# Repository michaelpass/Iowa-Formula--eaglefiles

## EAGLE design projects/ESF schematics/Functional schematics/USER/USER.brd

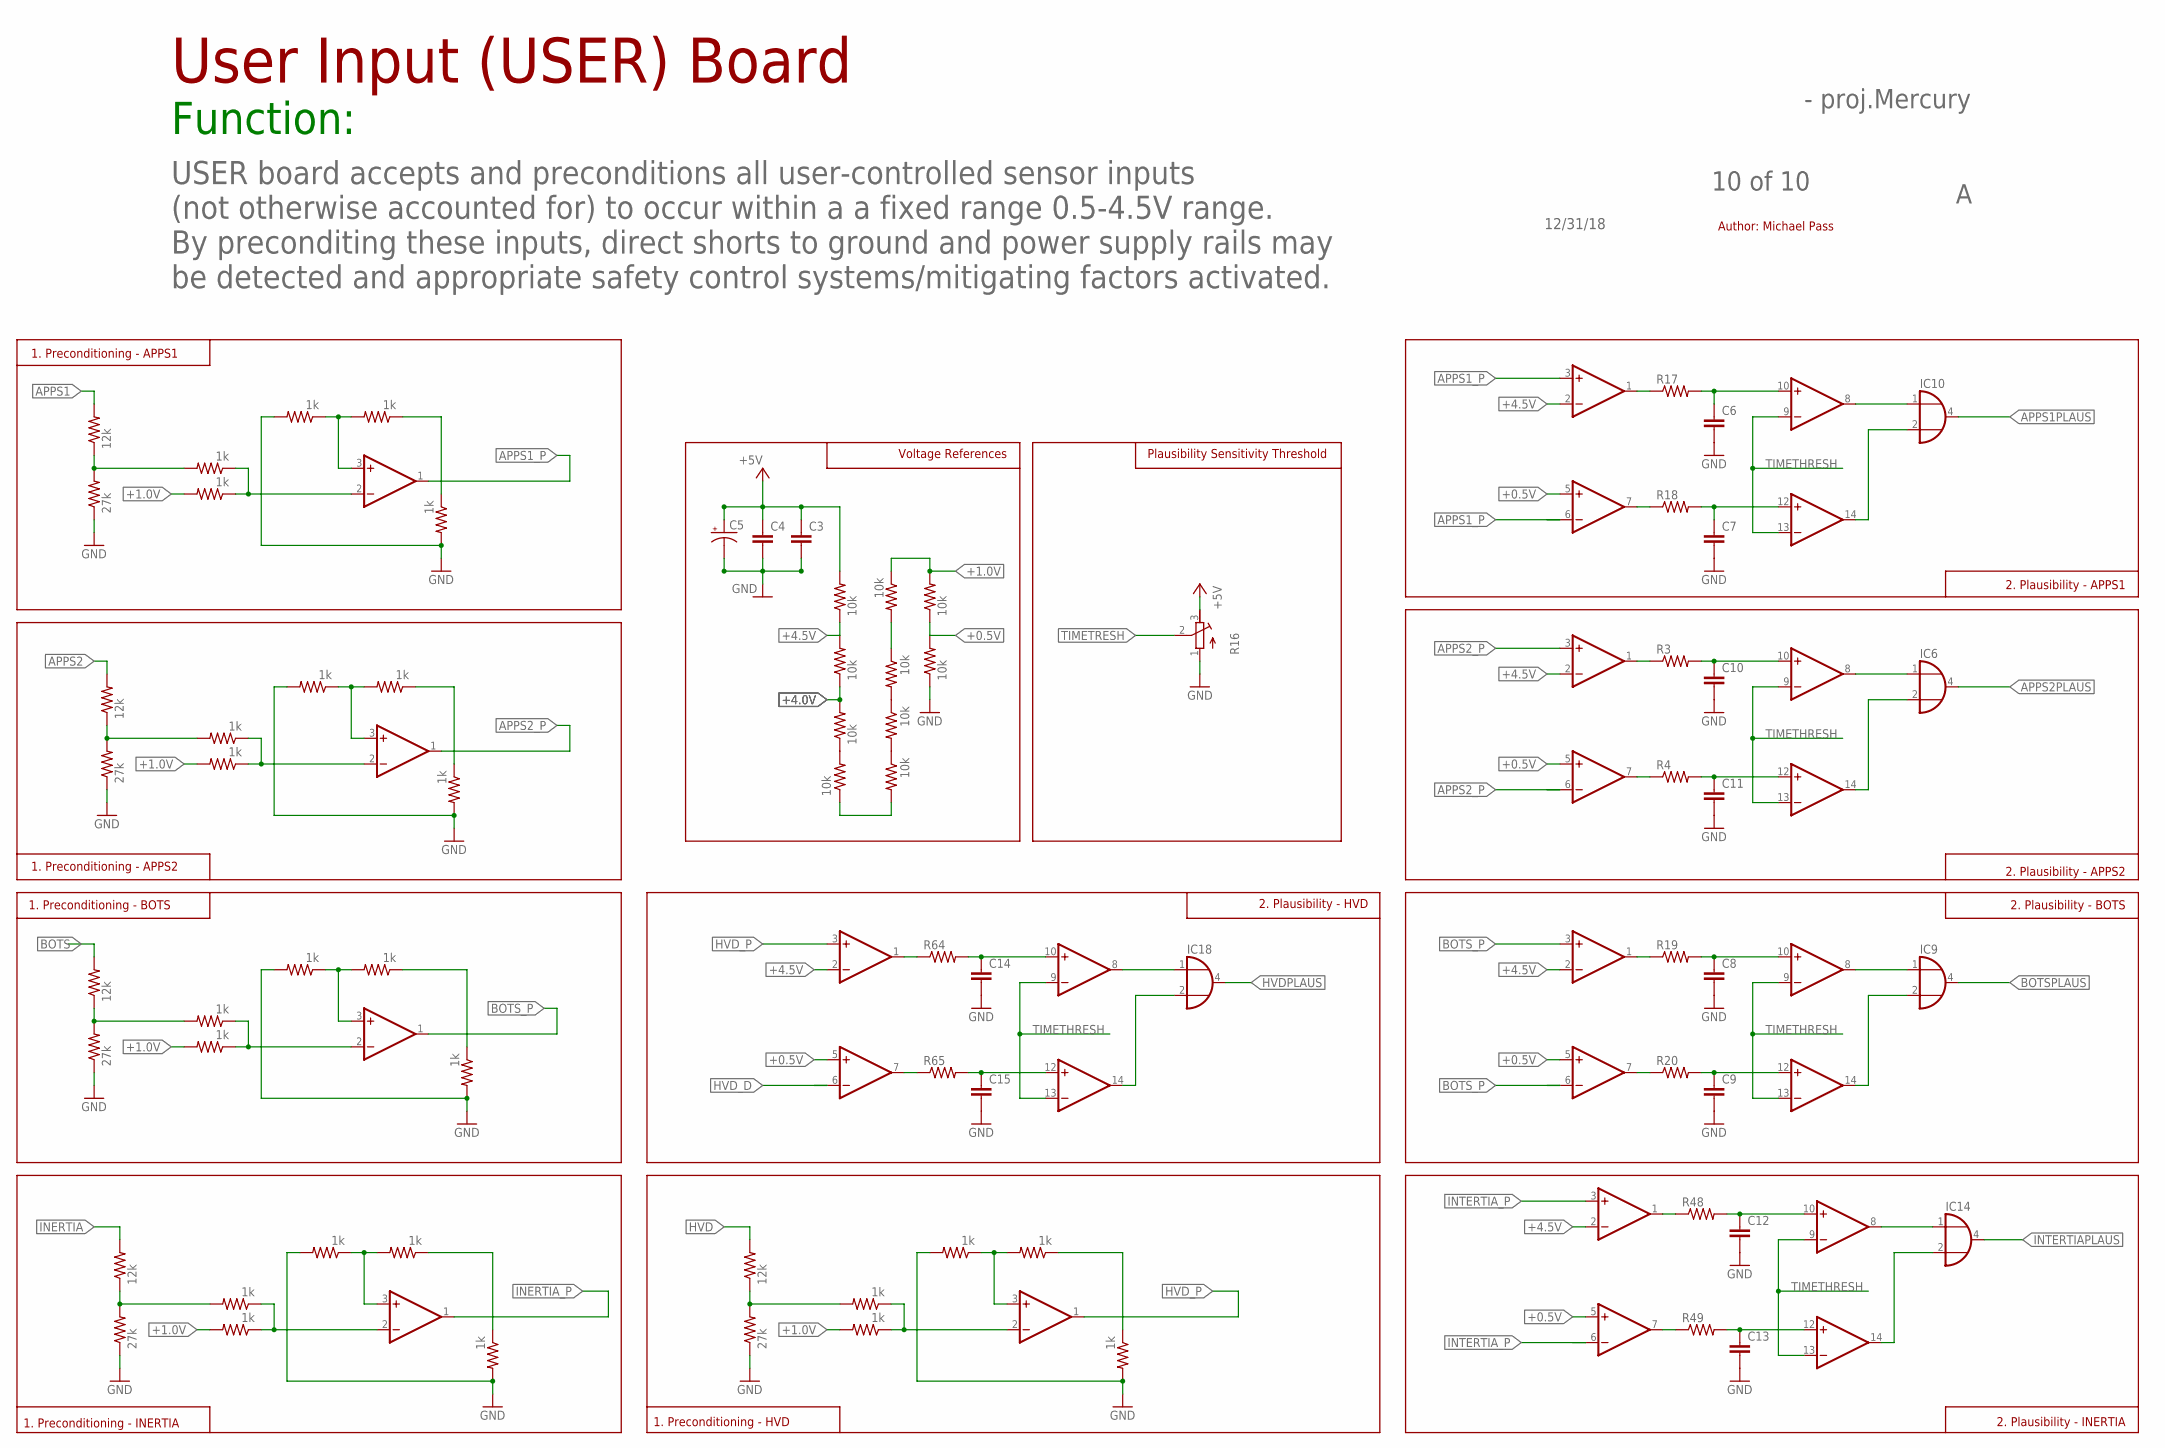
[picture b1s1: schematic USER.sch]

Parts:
C3, C4, C6, C7, C8, C9, C10, C11, C12, C13, C14, C15: C-EUC0805; C0805
C5: CPOL-US085CS-1AR; 085CS_1AR
IC1, IC3, IC4, IC5, IC7, IC8, IC13, IC17, IC19, IC20: OP11D; SO14
IC6, IC9, IC10, IC14, IC18: 74AHC1G32DCK; SC70-5
R1, R7, R71, R78, R85: 12k; R0805
R2, R21, R72, R79, R86: 27k; R0805
R3, R4, R17, R18, R19, R20, R48, R49, R64, R65: R-US_R0805; R0805
R5, R6, R8, R9, R10, R11, R12, R13, R14, R15: 10k; R0805
R16: R-TRIMM3224X; RTRIM3224X
R22, R23, R24, R25, R26, R66, R67, R68, R69, R70, R73, R74, R75, R76, R77, R80, R81, R82, R83, R84, R87, R88, R89, R90, R91: 1k; R0805

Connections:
+0.5V: IC1.5 (+IN), IC4.5 (+IN), IC5.5 (+IN), IC13.5 (+IN), IC17.5 (+IN), R14.1, R15.2
+1.0V: R13.1, R14.2, R23.2, R67.2, R74.2, R81.2, R88.2
+4.0V: R6.1, R8.2
+4.5V: IC1.2 (-IN), IC4.2 (-IN), IC5.2 (-IN), IC13.2 (-IN), IC17.2 (-IN), R5.1, R6.2
+5V: C3.1, C4.1, C5.+, R5.2, R16.3 (E)
APPS1: R71.2
APPS1PLAUS: IC10.4 (O)
APPS1_P: IC5.3 (+IN), IC5.6 (-IN), IC7.1 (OUT)
APPS2: R78.2
APPS2PLAUS: IC6.4 (O)
APPS2_P: IC1.3 (+IN), IC1.6 (-IN), IC19.1 (OUT)
BOTS: R7.2
BOTSPLAUS: IC9.4 (O)
BOTS_P: IC4.3 (+IN), IC4.6 (-IN), IC8.1 (OUT)
GND: C3.2, C4.2, C5.-, C6.2, C7.2, C8.2, C9.2, C10.2, C11.2, C12.2, C13.2, C14.2, C15.2, IC6.3 (GND), IC9.3 (GND), IC10.3 (GND), IC14.3 (GND), IC18.3 (GND), R2.1, R15.1, R16.1 (A), R21.1, R24.2, R26.2, R68.2, R70.2, R72.1, R75.2, R77.2, R79.1, R82.2, R84.2, R86.1, R89.2, R91.2
HVD: R85.2
HVDPLAUS: IC18.4 (O)
HVD_D: IC17.6 (-IN)
HVD_P: IC17.3 (+IN), IC20.1 (OUT)
INERTIA: R1.2
INERTIA_P: IC3.1 (OUT)
INTERTIAPLAUS: IC14.4 (O)
INTERTIA_P: IC13.3 (+IN), IC13.6 (-IN)
unnamed: IC3.3 (+IN), R68.1, R69.2
unnamed: R8.1, R9.2
unnamed: IC4.1 (OUT), R19.1
unnamed: R9.1, R10.2
unnamed: R11.1, R12.2
unnamed: IC5.1 (OUT), R17.1
unnamed: R12.1, R13.2
unnamed: R1.1, R2.2, R66.2
unnamed: R10.1, R11.2
unnamed: R69.1, R70.1
unnamed: IC3.2 (-IN), R66.1, R67.1
unnamed: C6.1, IC5.10 (+IN), R17.2
unnamed: C7.1, IC5.12 (+IN), R18.2
unnamed: IC5.7 (OUT), R18.1
unnamed: IC1.1 (OUT), R3.1
unnamed: C10.1, IC1.10 (+IN), R3.2
unnamed: C11.1, IC1.12 (+IN), R4.2
unnamed: IC1.7 (OUT), R4.1
unnamed: C8.1, IC4.10 (+IN), R19.2
unnamed: C9.1, IC4.12 (+IN), R20.2
unnamed: IC4.7 (OUT), R20.1
unnamed: IC1.8 (OUT), IC6.1 (I0)
unnamed: IC1.14 (OUT), IC6.2 (I1)
unnamed: IC8.3 (+IN), R24.1, R25.2
unnamed: R7.1, R21.2, R22.2
unnamed: R25.1, R26.1
unnamed: IC8.2 (-IN), R22.1, R23.1
unnamed: IC4.8 (OUT), IC9.1 (I0)
unnamed: IC4.14 (OUT), IC9.2 (I1)
unnamed: IC13.1 (OUT), R48.1
unnamed: C12.1, IC13.10 (+IN), R48.2
unnamed: IC7.3 (+IN), R75.1, R76.2
unnamed: R71.1, R72.2, R73.2
unnamed: IC5.8 (OUT), IC10.1 (I0)
unnamed: IC5.14 (OUT), IC10.2 (I1)
unnamed: C13.1, IC13.12 (+IN), R49.2
unnamed: IC13.7 (OUT), R49.1
unnamed: IC13.8 (OUT), IC14.1 (I0)
unnamed: IC13.14 (OUT), IC14.2 (I1)
unnamed: IC17.1 (OUT), R64.1
unnamed: C14.1, IC17.10 (+IN), R64.2
unnamed: C15.1, IC17.12 (+IN), R65.2
unnamed: IC17.7 (OUT), R65.1
unnamed: IC17.8 (OUT), IC18.1 (I0)
unnamed: IC17.14 (OUT), IC18.2 (I1)
unnamed: R76.1, R77.1
unnamed: IC7.2 (-IN), R73.1, R74.1
unnamed: IC19.3 (+IN), R82.1, R83.2
unnamed: R78.1, R79.2, R80.2
unnamed: R83.1, R84.1
unnamed: IC19.2 (-IN), R80.1, R81.1
unnamed: IC20.3 (+IN), R89.1, R90.2
unnamed: R85.1, R86.2, R87.2
unnamed: R90.1, R91.1
unnamed: IC20.2 (-IN), R87.1, R88.1
TIMETHRESH: IC1.9 (-IN), IC1.13 (-IN), IC4.9 (-IN), IC4.13 (-IN), IC5.9 (-IN), IC5.13 (-IN), IC13.9 (-IN), IC13.13 (-IN), IC17.9 (-IN), IC17.13 (-IN)
TIMETRESH: R16.2 (S)
V+: IC1.4 (V+), IC3.4 (V+), IC4.4 (V+), IC5.4 (V+), IC7.4 (V+), IC8.4 (V+), IC13.4 (V+), IC17.4 (V+), IC19.4 (V+), IC20.4 (V+)
V-: IC1.11 (V-), IC3.11 (V-), IC4.11 (V-), IC5.11 (V-), IC7.11 (V-), IC8.11 (V-), IC13.11 (V-), IC17.11 (V-), IC19.11 (V-), IC20.11 (V-)
VCC: IC6.5 (VCC), IC9.5 (VCC), IC10.5 (VCC), IC14.5 (VCC), IC18.5 (VCC)

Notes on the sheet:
12/31/18
10 of 10
- proj.Mercury
User Input (USER) Board
Function:
USER board accepts and preconditions all user-controlled sensor inputs (not otherwise accounted for) to occur within a a fixed range 0.5-4.5V range. By preconditing these inputs, direct shorts to ground and power supply rails may be detected and appropriate safety control systems/mitigating factors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
1. Preconditioning - APPS1
1. Preconditioning - APPS2
1. Preconditioning - BOTS
1. Preconditioning - INERTIA
1. Preconditioning - HVD
2. Plausibility - HVD
Voltage References
Plausibility Sensitivity Threshold
2. Plausibility - APPS1
2. Plausibility - APPS2
2. Plausibility - BOTS
2. Plausibility - INERTIA
Author: Michael Pass

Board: 2 copper layers, 84 parts (0 on the bottom side), 70 nets, no tracks yet.

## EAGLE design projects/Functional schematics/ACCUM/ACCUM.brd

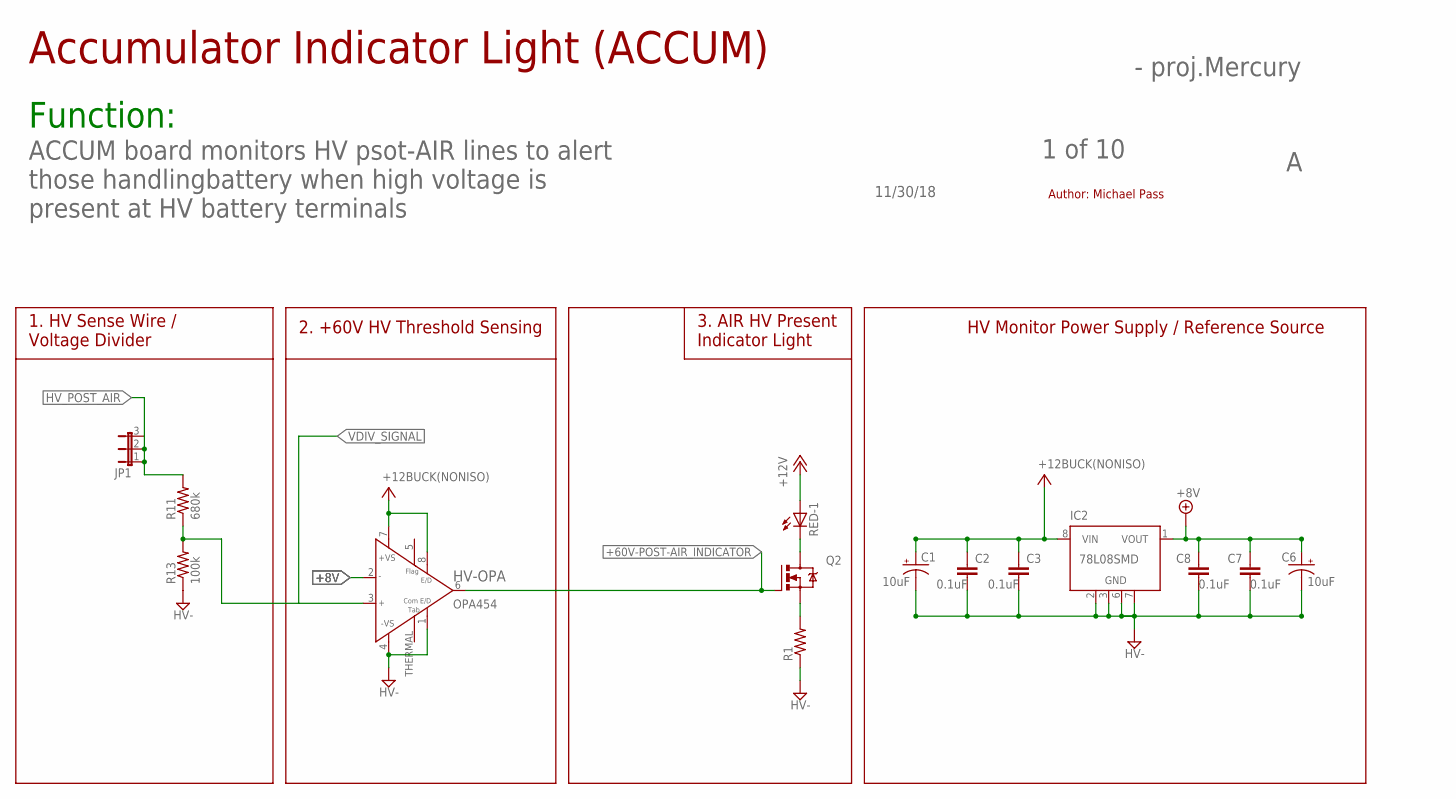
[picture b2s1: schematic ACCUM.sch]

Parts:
C1, C6: 10uF; 085CS_1AW
C2, C3, C7, C8: 0.1uF; C0805
HV-OPA: OPA454; SO08GP
IC2: 78L08SMD; SO08
JP1: JP2W
Q2: IRLZ44Z; TO220BH
R1: R-US_R0805; R0805
R11: 680k; R0805
R13: 100k; R0805
RED: LZR184

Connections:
+8V: C6.+, C7.1, C8.1, HV-OPA.2 (IN-), IC2.1 (VOUT)
+12V: RED.A1 (A)
+60V-POST-AIR_INDICATOR: HV-OPA.6 (OUT), Q2.G
GND: R1.1, R13.1
HV-: C1.-, C2.2, C3.2, C6.-, C7.2, C8.2, HV-OPA.1 (E/DCOM), HV-OPA.4 (-VS), IC2.2 (GND), IC2.3 (GND), IC2.6 (GND), IC2.7 (GND)
HV_POST_AIR: JP1.1, JP1.2, JP1.3, R11.2
unnamed: Q2.D, RED.K1 (C)
unnamed: Q2.S, R1.2
V+: C1.+, C2.1, C3.1, HV-OPA.7 (+VS), HV-OPA.8 (E/D), IC2.8 (VIN)
VDIV_SIGNAL: HV-OPA.3 (IN+), R11.1, R13.2

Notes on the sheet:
2. +60V HV Threshold Sensing
1. HV Sense Wire / Voltage Divider
HV Monitor Power Supply / Reference Source
3. AIR HV Present Indicator Light
Accumulator Indicator Light (ACCUM)
Function:
11/30/18
1 of 10
- proj.Mercury
ACCUM board monitors HV psot-AIR lines to alert those handlingbattery when high voltage is present at HV battery terminals
Author: Michael Pass

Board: 2 copper layers, 14 parts (0 on the bottom side), 9 nets, no tracks yet.

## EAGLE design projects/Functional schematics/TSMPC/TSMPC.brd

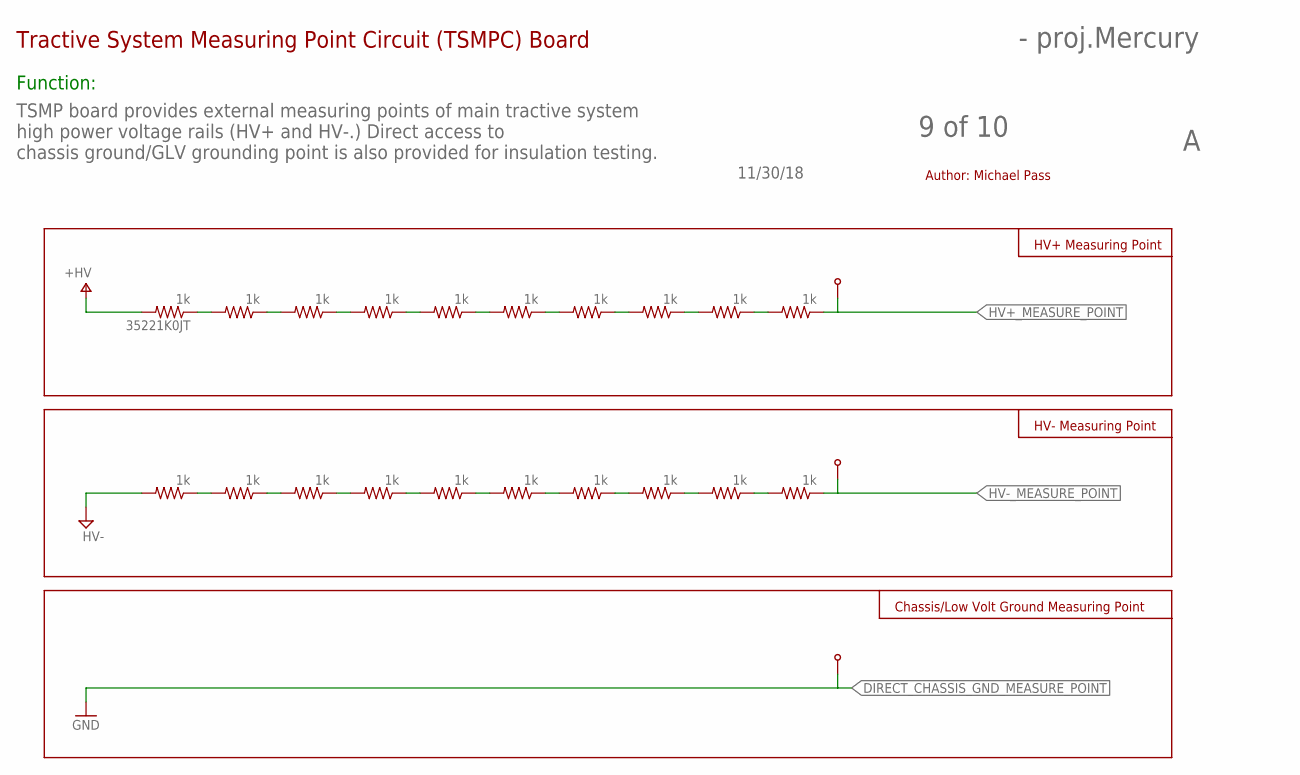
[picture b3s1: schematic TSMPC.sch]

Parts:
35221K0JT: 1k; R0805
R2, R3, R4, R5, R6, R7, R8, R9, R10, R21, R22, R23, R24, R25, R26, R27, R28, R29, R30: 1k; R0805
U$1, U$3, U$4: BANANA-JACK; BANANA-PRINT

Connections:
DIRECT_CHASSIS_GND_MEASURE_POINT: R21.2, U$3.P$1
HV+_MEASURE_POINT: R10.1, U$1.P$1
HV-_MEASURE_POINT: R30.1, U$4.P$1
unnamed: 35221K0JT.1, R2.2
unnamed: R2.1, R3.2
unnamed: R3.1, R4.2
unnamed: R4.1, R5.2
unnamed: R5.1, R6.2
unnamed: R6.1, R7.2
unnamed: R7.1, R8.2
unnamed: R8.1, R9.2
unnamed: R9.1, R10.2
unnamed: R21.1, R22.2
unnamed: R22.1, R23.2
unnamed: R23.1, R24.2
unnamed: R24.1, R25.2
unnamed: R25.1, R26.2
unnamed: R26.1, R27.2
unnamed: R27.1, R28.2
unnamed: R28.1, R29.2
unnamed: R29.1, R30.2
V+: 35221K0JT.2

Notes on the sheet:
Tractive System Measuring Point Circuit (TSMPC) Board
Function:
11/30/18
9 of 10
- proj.Mercury
TSMP board provides external measuring points of main tractive system high power voltage rails (HV+ and HV-.) Direct access to chassis ground/GLV grounding point is also provided for insulation testing.
Author: Michael Pass
HV+ Measuring Point
HV- Measuring Point
Chassis/Low Volt Ground Measuring Point

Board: 2 copper layers, 23 parts (0 on the bottom side), 21 nets, no tracks yet.

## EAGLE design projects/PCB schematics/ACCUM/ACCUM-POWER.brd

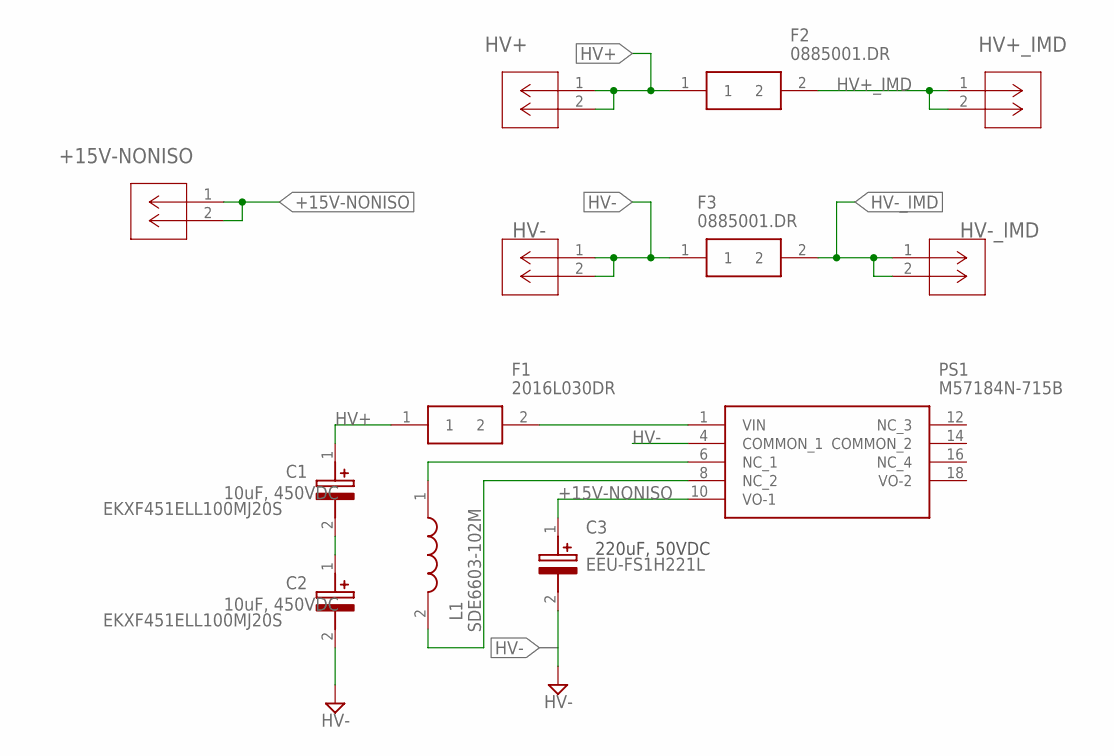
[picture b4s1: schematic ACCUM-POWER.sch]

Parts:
+15V-NONISO: 2P(90DEG)_1-770966-0; CON2_1X2_P163_RAMNL
C1, C2: EKXF451ELL100MJ20S; CAPPRD500W60D1025H2150
C3: EEU-FS1H221L; CAPPRD350W65D800H2200
F1: 2016L030DR; FUSC5141X125N
F2, F3: 0885001.DR; FUSC10948X488N
HV+: 2P(90DEG)_1-770966-0; CON2_1X2_P163_RAMNL
HV+_IMD: 2P(90DEG)_1-770966-0; CON2_1X2_P163_RAMNL
HV-: 2P(90DEG)_1-770966-0; CON2_1X2_P163_RAMNL
HV-_IMD: 2P(90DEG)_1-770966-0; CON2_1X2_P163_RAMNL
L1: SDE6603-102M; SDE6603
PS1: M57184N-715B; M57184N715B

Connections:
+15V-NONISO: +15V-NONISO.1, +15V-NONISO.2, C3.1 (+), PS1.10 (VO-1)
HV+: C1.1 (+), F1.1, F2.1, HV+.1, HV+.2
HV+_IMD: F2.2, HV+_IMD.1, HV+_IMD.2
HV-: C2.2 (-), C3.2 (-), F3.1, HV-.1, HV-.2, PS1.4 (COMMON_1)
HV-_IMD: F3.2, HV-_IMD.1, HV-_IMD.2
unnamed: L1.2, PS1.8 (NC_2)
unnamed: L1.1, PS1.6 (NC_1)
unnamed: C1.2 (-), C2.1 (+)
unnamed: F1.2, PS1.1 (VIN)

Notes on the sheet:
220uF, 50VDC
10uF, 450VDC

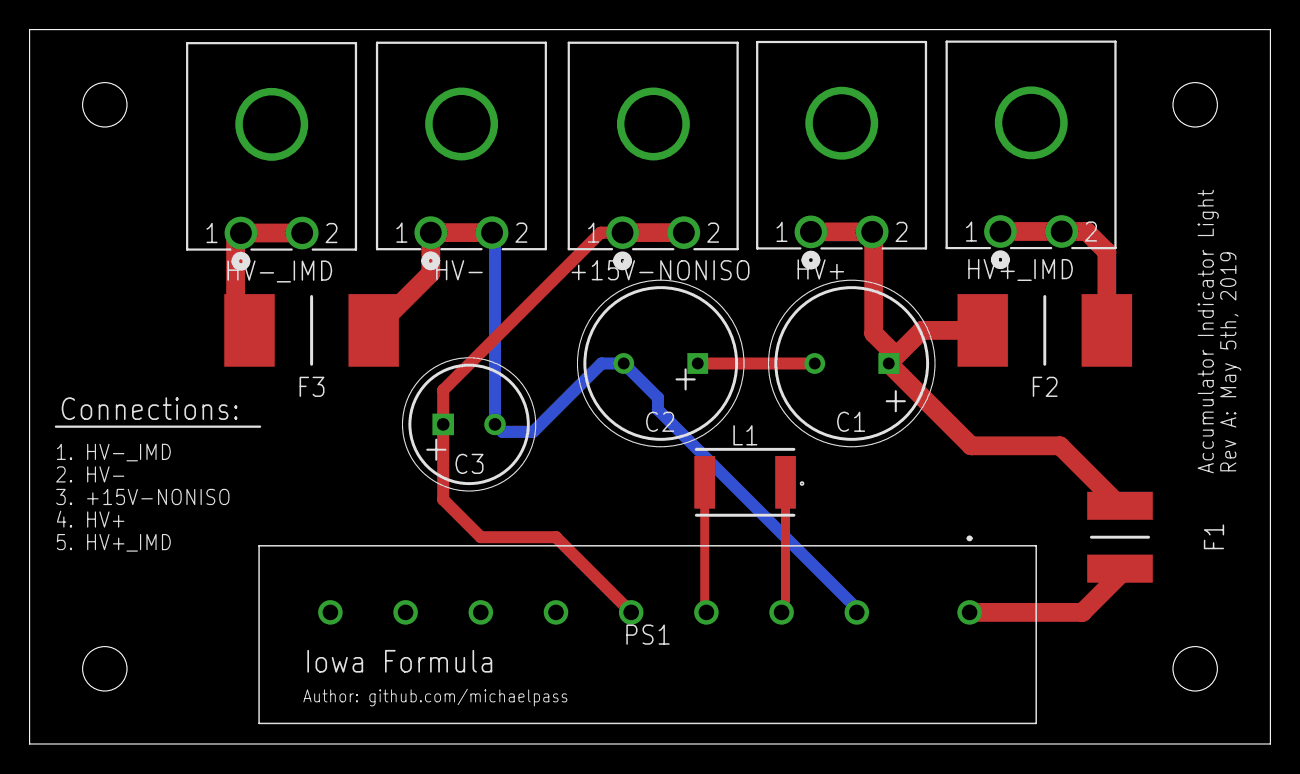
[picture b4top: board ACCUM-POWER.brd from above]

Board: 2 copper layers, 83.8 x 48.3 mm, 13 parts (0 on the bottom side), 9 nets.

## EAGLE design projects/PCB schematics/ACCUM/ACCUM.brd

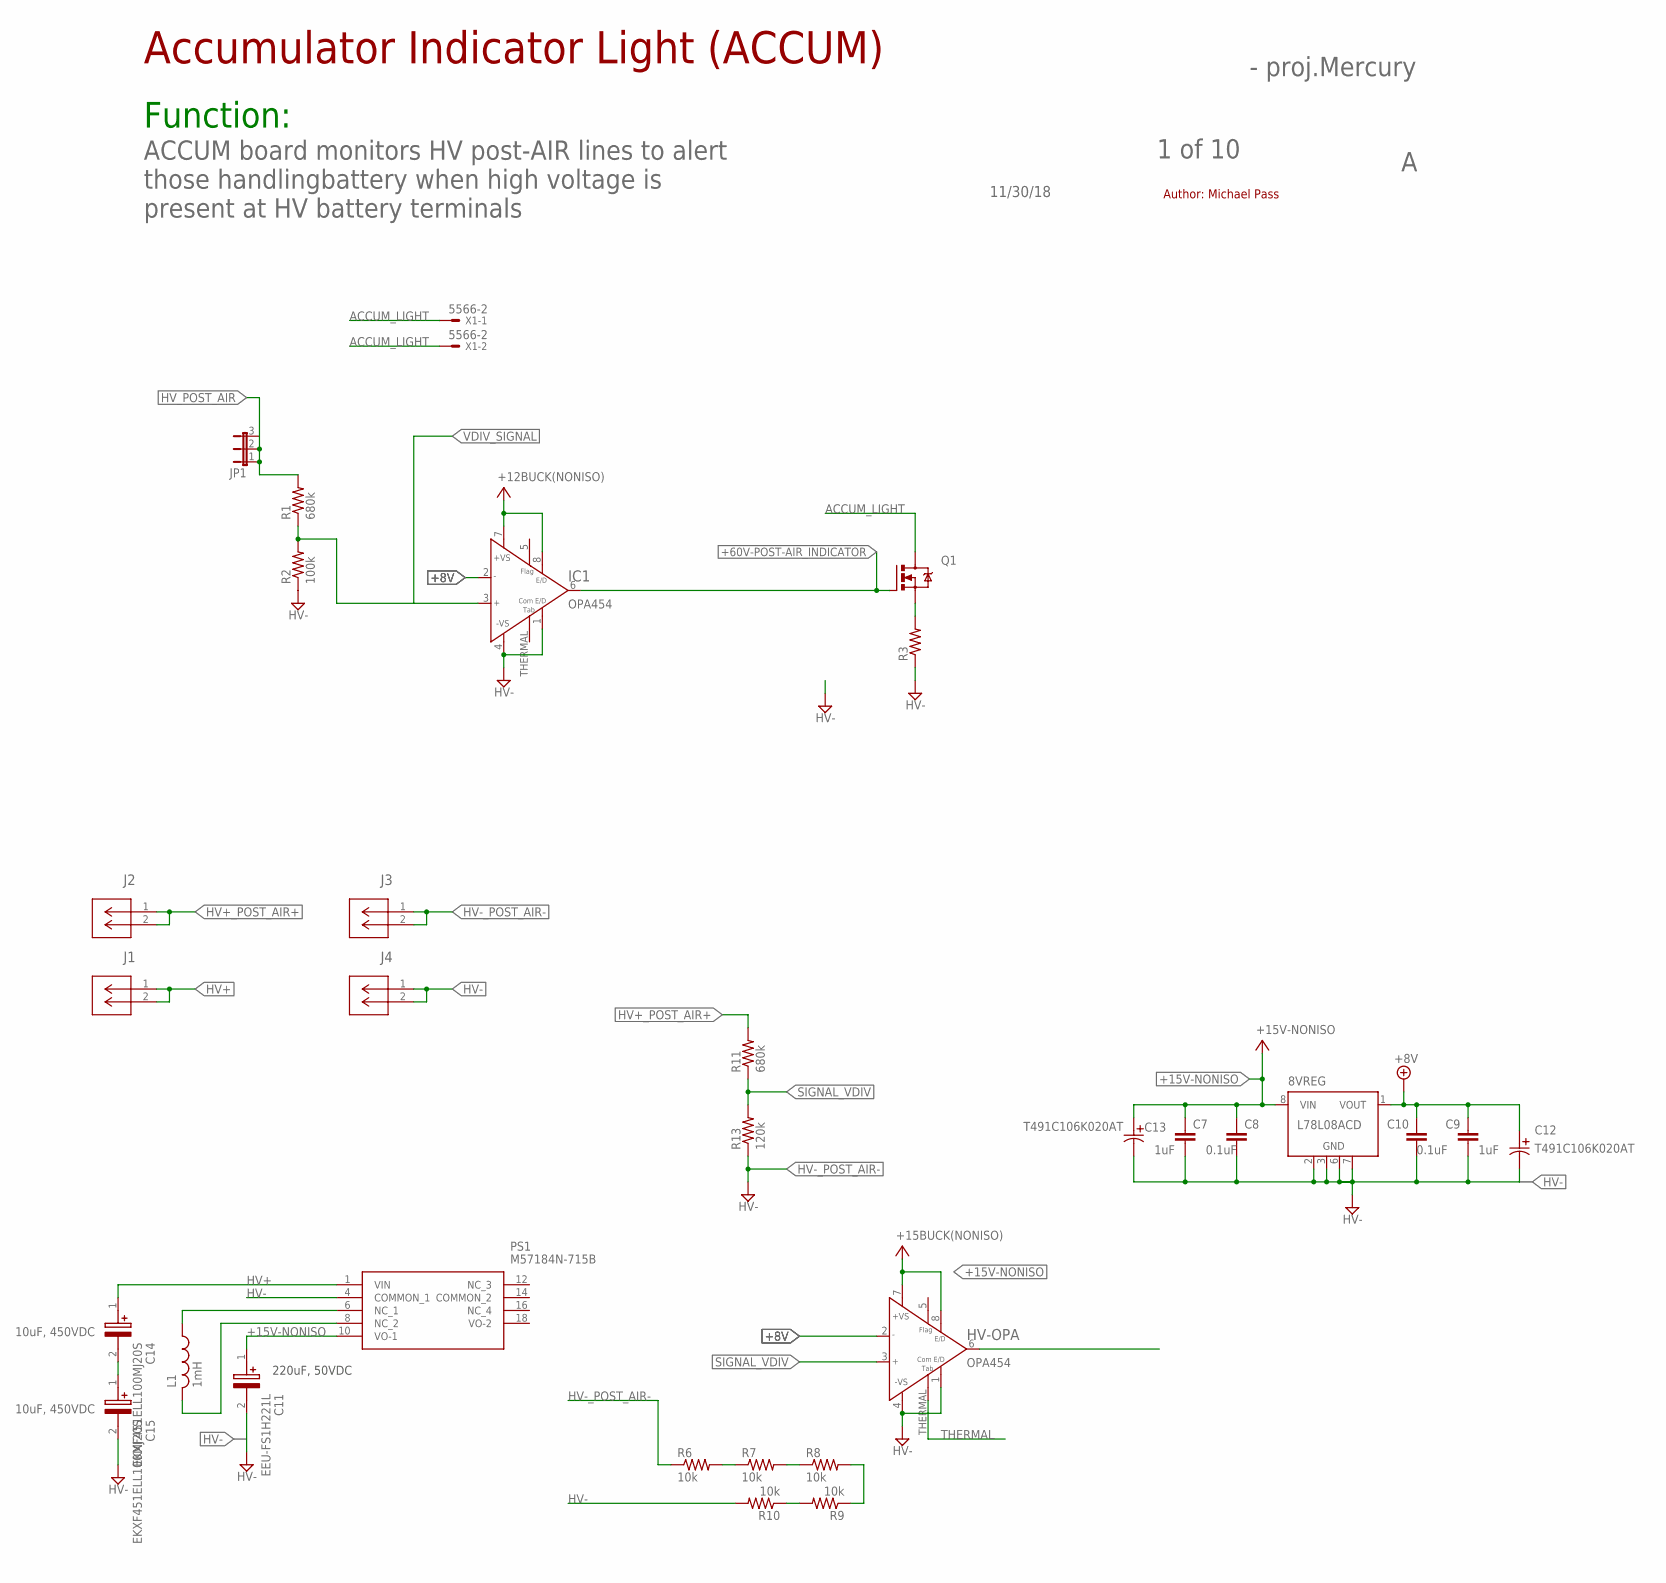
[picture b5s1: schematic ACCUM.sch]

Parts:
8VREG: L78L08ACD; SO08
C7, C9: 1uF; C0805
C8, C10: 0.1uF; C0805
C11: EEU-FS1H221L; CAPPRD350W65D800H2200
C12, C13: T491C106K020AT; CAPT6032N
C14, C15: EKXF451ELL100MJ20S; CAPPRD500W60D1025H2150
HV-OPA: OPA454; SO08GP
IC1: OPA454; SO08GP
J1, J2, J3, J4: 2P_1-770166-0; CON2_1X2_P163_VMNL-1MTG
JP1: JP2W
L1: 1mH; L2012C
PS1: M57184N-715B; M57184N715B
Q1: IRLZ44Z; TO220BH
R1, R11: 680k; R0805
R2: 100k; R0805
R3: R-US_R0805; R0805
R6, R7, R8, R9, R10: 10k; R0805
R13: 120k; R0805
X1: 5566-2

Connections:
+8V: 8VREG.1 (VOUT), C9.1, C10.1, C12.1, HV-OPA.2 (IN-), IC1.2 (IN-)
+15V-NONISO: 8VREG.8 (VIN), C7.1, C8.1, C11.1 (+), C13.1, HV-OPA.7 (+VS), HV-OPA.8 (E/D), PS1.10 (VO-1)
+60V-POST-AIR_INDICATOR: IC1.6 (OUT), Q1.G
ACCUM_LIGHT: Q1.D, X1.1, X1.2
GND: R2.1, R3.1
HV+: C14.1 (+), J1.1, J1.2, PS1.1 (VIN)
HV+_POST_AIR+: J2.1, J2.2, R11.2
HV-: 8VREG.2 (GND), 8VREG.3 (GND), 8VREG.6 (GND), 8VREG.7 (GND), C7.2, C8.2, C9.2, C10.2, C11.2 (-), C12.2, C13.2, C15.2 (-), HV-OPA.1 (E/DCOM), HV-OPA.4 (-VS), IC1.1 (E/DCOM), IC1.4 (-VS), J4.1, J4.2, PS1.4 (COMMON_1), R10.2
HV-_POST_AIR-: J3.1, J3.2, R6.1, R13.1
HV_POST_AIR: JP1.1, JP1.2, JP1.3, R1.2
unnamed: L1.2, PS1.8 (NC_2)
unnamed: L1.1, PS1.6 (NC_1)
unnamed: C14.2 (-), C15.1 (+)
unnamed: R7.2, R8.1
unnamed: R6.2, R7.1
unnamed: Q1.S, R3.2
unnamed: R8.2, R9.1
unnamed: R9.2, R10.1
SIGNAL_VDIV: HV-OPA.3 (IN+), R11.1, R13.2
THERMAL: HV-OPA.THERMAL (E/DCOM1)
V+: IC1.7 (+VS), IC1.8 (E/D)
VDIV_SIGNAL: IC1.3 (IN+), R1.1, R2.2

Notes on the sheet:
Accumulator Indicator Light (ACCUM)
Function:
11/30/18
1 of 10
- proj.Mercury
ACCUM board monitors HV post-AIR lines to alert those handlingbattery when high voltage is present at HV battery terminals
Author: Michael Pass
220uF, 50VDC
10uF, 450VDC

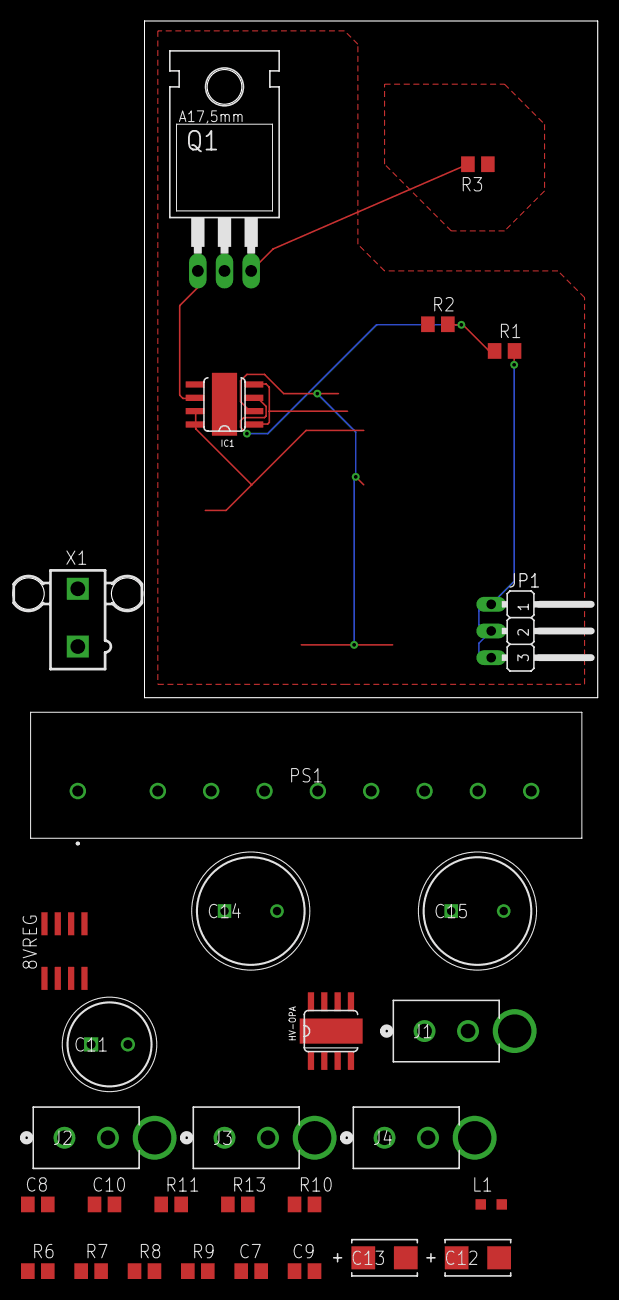
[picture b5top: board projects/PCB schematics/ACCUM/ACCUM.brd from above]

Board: 2 copper layers, 43.2 x 64.4 mm, 31 parts (0 on the bottom side), 21 nets.
